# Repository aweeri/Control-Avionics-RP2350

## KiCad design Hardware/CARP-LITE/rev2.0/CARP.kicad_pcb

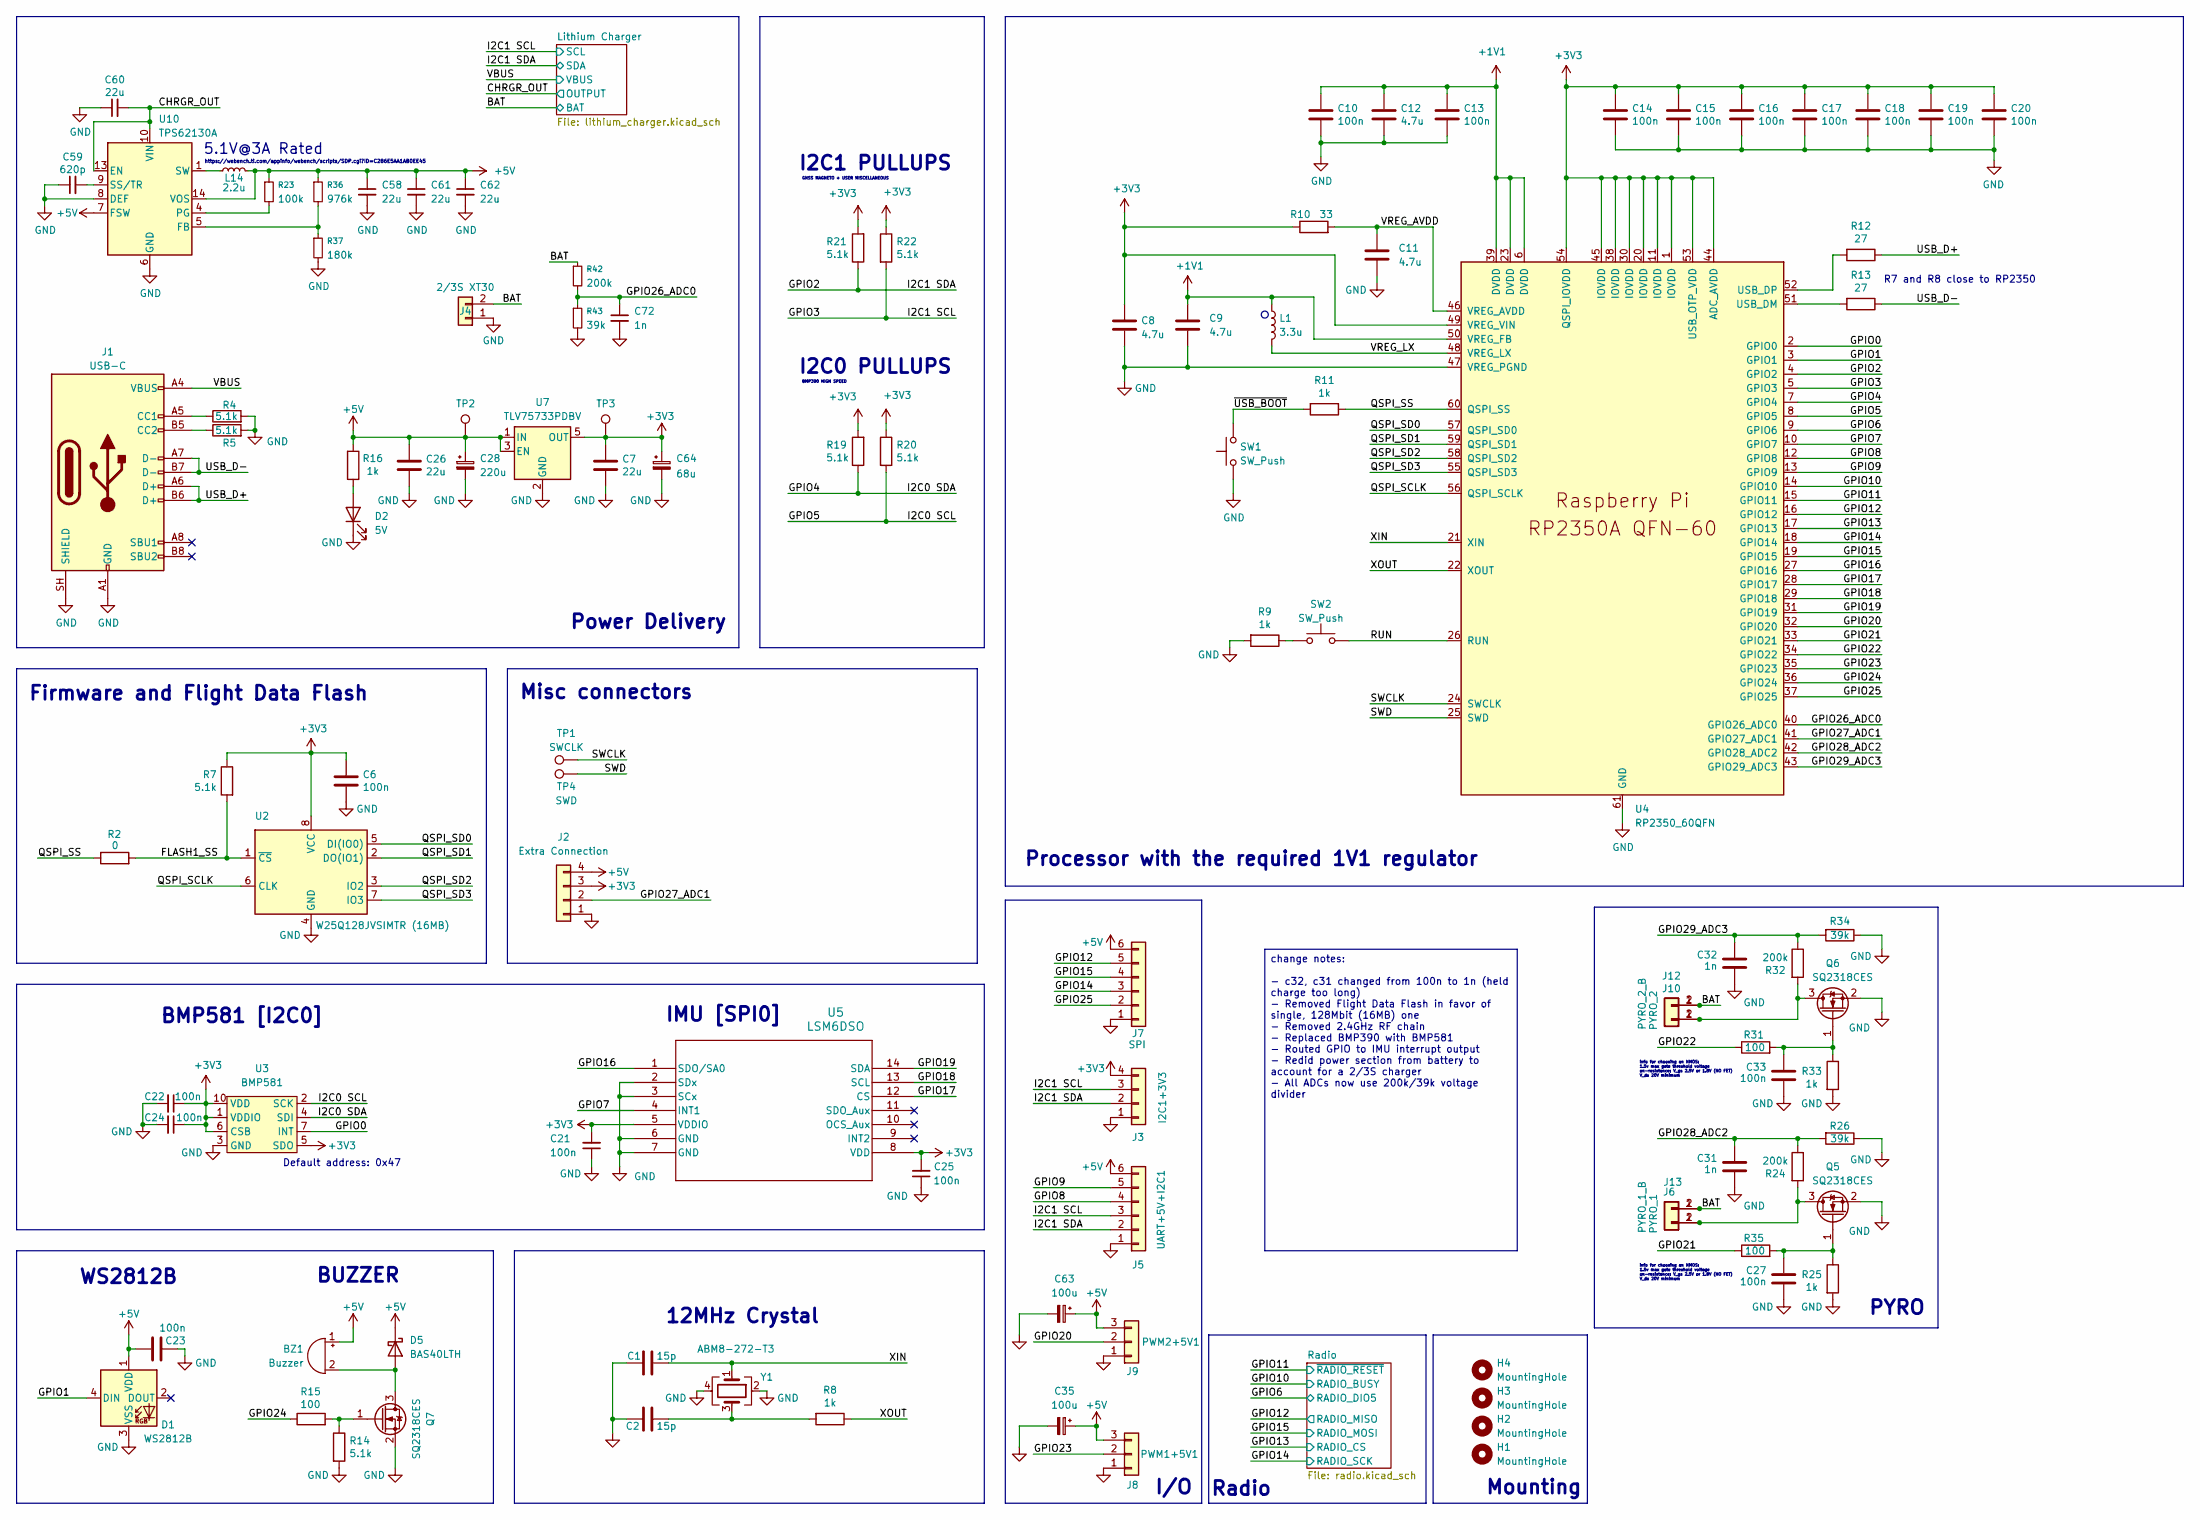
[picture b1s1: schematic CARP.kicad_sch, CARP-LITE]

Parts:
BZ1: Buzzer; Buzzer_12x9.5RM7.6
C1, C2: 15p; C_0402_1005Metric
C6, C10, C13, C14, C15, C16, C17, C18, C19, C20, C21, C22, C23, C24, C25, C27, C33: 100n; C_0402_1005Metric
C7, C26, C58, C60, C61, C62: 22u; C_0805_2012Metric
C8, C9: 4.7u; C_0402_1005Metric_small_pads
C11, C12: 4.7u; C_0402_1005Metric
C28: 220u; CP_EIA-7343-31_Kemet-D
C31, C32, C72: 1n; C_0402_1005Metric
C35, C63: 100u; CP_EIA-6032-28_Kemet-C
C59: 620p; C_0402_1005Metric
C64: 68u; CP_EIA-3528-21_Kemet-B
D1: WS2812B; LED_WS2812B_PLCC4_5.0x5.0mm_P3.2mm
D2: 5V; LED_0805_2012Metric
D5: BAS40LTH; D_SOD-882
H1, H2, H3, H4: MountingHole; MountingHole_3.2mm_M3_DIN965_Pad_TopBottom
J1: USB-C; USB_C_Receptacle_GCT_USB4105-xx-A_16P_TopMnt_Horizontal
J2: Extra Connection; Molex_PicoBlade_53047-0410_1x04_P1.25mm_Vertical
J3: I2C1+3V3; Molex_PicoBlade_53047-0410_1x04_P1.25mm_Vertical
J4: 2/3S XT30; AMASS_XT30PW-M_1x02_P2.50mm_Horizontal
J5: UART+5V+I2C1; Molex_PicoBlade_53047-0610_1x06_P1.25mm_Vertical
J6: PYRO_1; Molex_Nano-Fit_105309-xx02_1x02_P2.50mm_Vertical
J7: SPI; Molex_PicoBlade_53047-0610_1x06_P1.25mm_Vertical
J8: PWM1+5V1; Molex_PicoBlade_53047-0310_1x03_P1.25mm_Vertical
J9: PWM2+5V1; Molex_PicoBlade_53047-0310_1x03_P1.25mm_Vertical
J10: PYRO_2; Molex_Nano-Fit_105309-xx02_1x02_P2.50mm_Vertical
J12: PYRO_2_B; Molex_Nano-Fit_105313-xx02_1x02_P2.50mm_Horizontal
J13: PYRO_1_B; Molex_Nano-Fit_105313-xx02_1x02_P2.50mm_Horizontal
L1: 3.3u; L_pol_2016
L14: 2.2u; L_Coilcraft_XxL4020
Q5, Q6, Q7: SQ2318CES; SOT-23
R2: 0; R_0603_1608Metric
R4, R5, R7, R14, R19, R20, R21, R22: 5.1k; R_0402_1005Metric
R8, R9, R11, R16, R25, R33: 1k; R_0402_1005Metric
R10: 33; R_0402_1005Metric
R12, R13: 27; R_0402_1005Metric
R15, R31, R35: 100; R_0402_1005Metric
R23: 100k; R_0402_1005Metric
R24, R32, R42: 200k; R_0402_1005Metric
R26, R34, R43: 39k; R_0402_1005Metric
R36: 976k; R_0402_1005Metric
R37: 180k; R_0402_1005Metric
SW1, SW2: SW_Push; SW_Push_1P1T_XKB_TS-1187A
TP1: SWCLK; TestPoint_Pad_D1.5mm
TP2, TP3: TestPoint; TestPoint_Pad_D1.5mm
TP4: SWD; TestPoint_Pad_D1.5mm
U2: W25Q128JVSIMTR (16MB); SOIC-8_5.3x5.3mm_P1.27mm
U3: BMP581; 10LGA_2X2X0p75_BOS
U4: RP2350_60QFN; RP2350-QFN-60-1EP_7x7_P0.4mm_EP3.4x3.4mm_ThermalVias
U5: LSM6DSO; LGA-14L_2P5X3X0P86_STM
U7: TLV75733PDBV; SOT-23-5
U10: TPS62130A; VQFN-16-1EP_3x3mm_P0.5mm_EP1.68x1.68mm_ThermalVias
Y1: ABM8-272-T3; Crystal_SMD_3225-4Pin_3.2x2.5mm

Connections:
+1V1: C9.1, C10.1, C12.1, C13.1, L1.1, U4.6 (DVDD), U4.23 (DVDD), U4.39 (DVDD), U4.50 (VREG_FB)
+3V3: C6.1, C7.1, C8.1, C14.1, C15.1, C16.1, C17.1, C18.1, C19.1, C20.1, C21.2, C22.1, C24.1, C25.2, C64.1, J2.3, J3.4, R7.1, R10.1, R19.2, R20.1, R21.2, R22.1, TP3.1 (1_1), U2.8 (VCC), U3.1 (VDDIO), U3.5 (SDO), U3.6 (CSB), U3.10 (VDD), U4.1 (IOVDD), U4.11 (IOVDD), U4.20 (IOVDD), U4.30 (IOVDD), U4.38 (IOVDD), U4.44 (ADC_AVDD), U4.45 (IOVDD), U4.49 (VREG_VIN), U4.53 (USB_OTP_VDD), U4.54 (QSPI_IOVDD), U5.5 (VDDIO), U5.8 (VDD), U7.5 (OUT); also elsewhere on the board
+5V: BZ1.1 (+), C23.1, C26.1, C28.1, C35.1, C58.1, C61.1, C62.1, C63.1, D1.1 (VDD), D5.1 (K), J2.4, J5.6, J7.6, J8.3, J9.3, L14.2, R16.2, R23.1, R36.1, TP2.1 (1_1), U7.1 (IN), U7.3 (EN), U10.7 (FSW), U10.14 (VOS)
/BAT: J4.2, J6.1, J10.1, J12.2, J13.2, R42.1; also elsewhere on the board
/CHRGR_OUT: C60.2, U10.10 (VIN), U10.11 (VIN), U10.12 (VIN), U10.13 (EN); also elsewhere on the board
/FLASH1_SS: R2.2, R7.2, U2.1 (~CS)
/GPIO0: U3.7 (INT), U4.2 (GPIO0)
/GPIO1: D1.4 (DIN), U4.3 (GPIO1)
/GPIO2: J3.2, J5.2, R21.1, U4.4 (GPIO2); also elsewhere on the board
/GPIO3: J3.3, J5.3, R22.2, U4.5 (GPIO3); also elsewhere on the board
/GPIO4: R19.1, U3.4 (SDI), U4.7 (GPIO4)
/GPIO5: R20.2, U3.2 (SCK), U4.8 (GPIO5)
/GPIO6: U4.9 (GPIO6); also elsewhere on the board
/GPIO7: U4.10 (GPIO7), U5.4 (INT1)
/GPIO8: J5.4, U4.12 (GPIO8)
/GPIO9: J5.5, U4.13 (GPIO9)
/GPIO10: U4.14 (GPIO10); also elsewhere on the board
/GPIO11: U4.15 (GPIO11); also elsewhere on the board
/GPIO12: J7.5, U4.16 (GPIO12); also elsewhere on the board
/GPIO13: U4.17 (GPIO13); also elsewhere on the board
/GPIO14: J7.3, U4.18 (GPIO14); also elsewhere on the board
/GPIO15: J7.4, U4.19 (GPIO15); also elsewhere on the board
/GPIO16: U4.27 (GPIO16), U5.1 (SDO/SA0)
/GPIO17: U4.28 (GPIO17), U5.12 (CS)
/GPIO18: U4.29 (GPIO18), U5.13 (SCL)
/GPIO19: U4.31 (GPIO19), U5.14 (SDA)
/GPIO20: J9.2, U4.32 (GPIO20)
/GPIO21: R35.1, U4.33 (GPIO21)
/GPIO22: R31.1, U4.34 (GPIO22)
/GPIO23: J8.2, U4.35 (GPIO23)
/GPIO24: R15.1, U4.36 (GPIO24)
/GPIO26_ADC0: C72.1, R42.2, R43.1, U4.40 (GPIO26_ADC0)
/GPIO27_ADC1: J2.2, U4.41 (GPIO27_ADC1)
/GPIO28_ADC2: C31.2, R24.1, R26.2, U4.42 (GPIO28_ADC2)
/GPIO29_ADC3: C32.2, R32.1, R34.2, U4.43 (GPIO29_ADC3)
/QSPI_SCLK: U2.6 (CLK), U4.56 (QSPI_SCLK)
/QSPI_SD0: U2.5 (DI(IO0)), U4.57 (QSPI_SD0)
/QSPI_SD1: U2.2 (DO(IO1)), U4.59 (QSPI_SD1)
/QSPI_SD2: U2.3 (IO2), U4.58 (QSPI_SD2)
/QSPI_SD3: U2.7 (IO3), U4.55 (QSPI_SD3)
/QSPI_SS: R2.1, R11.1, U4.60 (QSPI_SS)
/RUN: SW2.2, U4.26 (RUN)
/SWCLK: TP1.1 (1_1), U4.24 (SWCLK)
/SWD: TP4.1 (1_1), U4.25 (SWD)
/USB_D+: J1.A6 (D+), J1.B6 (D+), R12.1
/USB_D-: J1.A7 (D-), J1.B7 (D-), R13.1
/VBUS: J1.A4 (VBUS), J1.A9 (VBUS), J1.B4 (VBUS), J1.B9 (VBUS); also elsewhere on the board
/VREG_AVDD: C11.1, R10.2, U4.46 (VREG_AVDD)
/VREG_LX: L1.2, U4.48 (VREG_LX)
/XIN: C1.1, U4.21 (XIN), Y1.1
/XOUT: R8.1, U4.22 (XOUT)
/~USB_BOOT: R11.2, SW1.2
unnamed: BZ1.2 (-), D5.2 (A), Q7.3 (D)
unnamed: C2.1, R8.2, Y1.3
unnamed: D2.2 (A), R16.1
unnamed: J1.A5 (CC1), R4.1
unnamed: J1.B5 (CC2), R5.1
unnamed: J10.2, J12.1, Q6.3 (D), R32.2
unnamed: J6.2, J13.1, Q5.3 (D), R24.2
unnamed: L14.1, U10.1 (SW), U10.2 (SW), U10.3 (SW)
unnamed: C27.2, Q5.1 (G), R25.1, R35.2
unnamed: C33.2, Q6.1 (G), R31.2, R33.1
unnamed: Q7.1 (G), R14.1, R15.2
unnamed: R9.1, SW2.1
unnamed: R13.2, U4.51 (USB_DM)
unnamed: R12.2, U4.52 (USB_DP)
unnamed: R36.2, R37.1, U10.5 (FB)
unnamed: R23.2, U10.4 (PG)
unnamed: C59.2, U10.9 (SS/TR)

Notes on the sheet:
BUZZER
5.1V@3A Rated
PYRO
info for choosing an NMOS: 1.5v max gate threshold voltage on-resistance: V_gs 2.5V or 1.8V (NO FET) V_ds 20V minimum
https://webench.ti.com/appinfo/webench/scripts/SDP.cgi?ID=C286E5AA1AB0EE45
Misc connectors
I2C1 PULLUPS
I2C0 PULLUPS
Firmware and Flight Data Flash
GNSS MAGNETO + USER MISCELLANEOUS
Radio
WS2812B
R7 and R8 close to RP2350
IMU [SPI0]
Default address: 0x47
I/O
Mounting
BMP581 [I2C0]
BMP390 HIGH SPEED
12MHz Crystal
Power Delivery
Processor with the required 1V1 regulator
change notes: - c32, c31 changed from 100n to 1n (held charge too long) - Removed Flight Data Flash in favor of single, 128Mbit (16MB) one - Removed 2.4GHz RF chain - Replaced BMP390 with BMP581 - Routed GPIO to IMU interrupt output - Redid power section from battery to account for a 2/3S charger -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

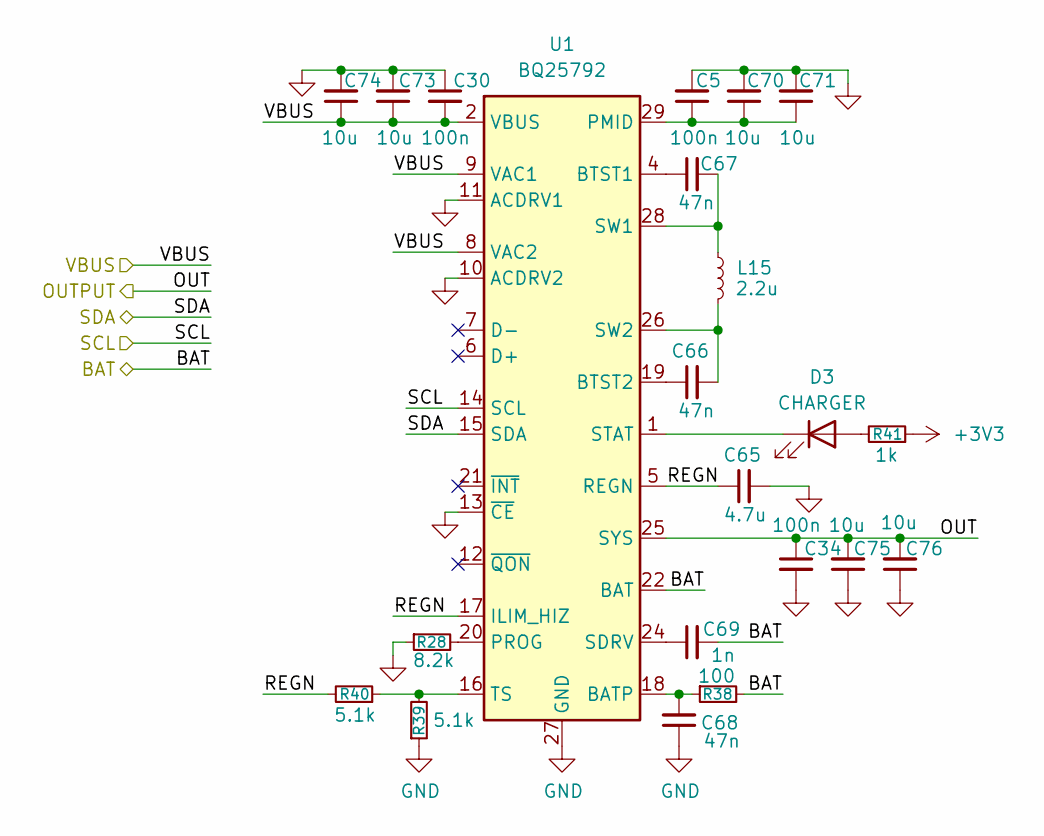
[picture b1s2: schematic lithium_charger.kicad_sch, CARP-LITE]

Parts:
C5, C30, C34: 100n; C_0402_1005Metric
C65: 4.7u; C_0603_1608Metric
C66, C67, C68: 47n; C_0402_1005Metric
C69: 1n; C_0402_1005Metric
C70, C71, C73, C74, C75, C76: 10u; C_0805_2012Metric
D3: CHARGER; LED_0805_2012Metric
L15: 2.2u; L_Coilcraft_XFL2010
R28: 8.2k; R_0402_1005Metric
R38: 100; R_0402_1005Metric
R39, R40: 5.1k; R_0402_1005Metric
R41: 1k; R_0402_1005Metric
U1: BQ25792; Texas_RQM0029A_VQFN-29_4x4mm_P0.4mm

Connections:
+3V3: R41.1; also elsewhere on the board
/BAT: C69.2, R38.2, U1.22 (BAT), U1.23 (BAT); also elsewhere on the board
/CHRGR_OUT: C34.1, C75.2, C76.2, U1.25 (SYS); also elsewhere on the board
/GPIO2: U1.15 (SDA); also elsewhere on the board
/GPIO3: U1.14 (SCL); also elsewhere on the board
/Lithium Charger/REGN: C65.1, R40.2, U1.5 (REGN), U1.17 (ILIM_HIZ)
/VBUS: C30.2, C73.1, C74.1, U1.2 (VBUS), U1.3 (VBUS), U1.8 (VAC2), U1.9 (VAC1); also elsewhere on the board
unnamed: D3.2 (A), R41.2
unnamed: D3.1 (K), U1.1 (STAT)
unnamed: C68.2, R38.1, U1.18 (BATP)
unnamed: C67.1, U1.4 (BTST1)
unnamed: C66.1, U1.19 (BTST2)
unnamed: C5.1, C70.1, C71.1, U1.29 (PMID)
unnamed: R28.2, U1.20 (PROG)
unnamed: C69.1, U1.24 (SDRV)
unnamed: C67.2, L15.1, U1.28 (SW1)
unnamed: C66.2, L15.2, U1.26 (SW2)
unnamed: R39.2, R40.1, U1.16 (TS)

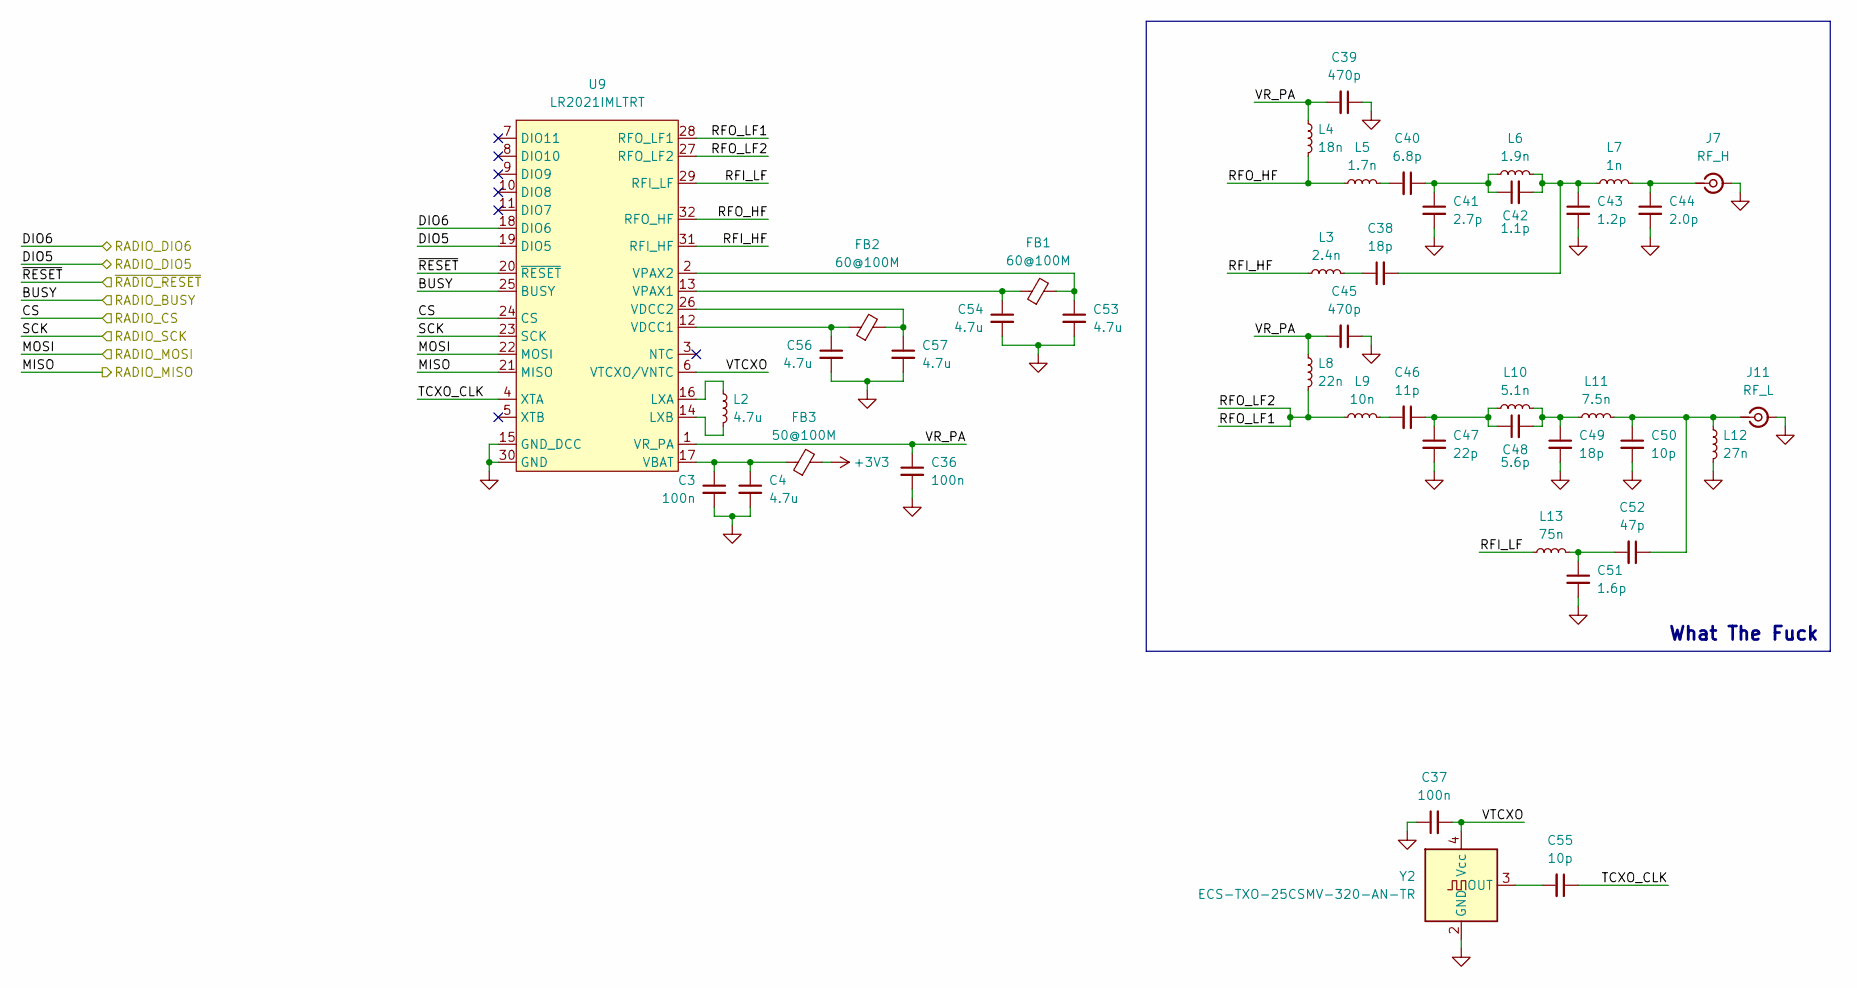
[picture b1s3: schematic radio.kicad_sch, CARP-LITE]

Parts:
C3, C36, C37: 100n; C_0603_1608Metric
C4, C53, C54, C56, C57: 4.7u; C_0603_1608Metric
C38, C49: 18p; C_0402_1005Metric
C39, C45: 470p; C_0402_1005Metric
C40: 6.8p; C_0402_1005Metric
C41: 2.7p; C_0402_1005Metric
C42: 1.1p; C_0402_1005Metric
C43: 1.2p; C_0402_1005Metric
C44: 2.0p; C_0402_1005Metric
C46: 11p; C_0402_1005Metric
C47: 22p; C_0402_1005Metric
C48: 5.6p; C_0402_1005Metric
C50, C55: 10p; C_0402_1005Metric
C51: 1.6p; C_0402_1005Metric
C52: 47p; C_0402_1005Metric
FB1, FB2: 60@100M; L_0603_1608Metric
FB3: 50@100M; L_0603_1608Metric
J7: RF_H; U.FL_Hirose_U.FL-R-SMT-1_Vertical
J11: RF_L; U.FL_Hirose_U.FL-R-SMT-1_Vertical
L2: 4.7u; L_1008_2520Metric
L3: 2.4n; L_0402_1005Metric
L4: 18n; L_0402_1005Metric
L5: 1.7n; L_0402_1005Metric
L6: 1.9n; L_0402_1005Metric
L7: 1n; L_0402_1005Metric
L8: 22n; L_0402_1005Metric
L9: 10n; L_0402_1005Metric
L10: 5.1n; L_0402_1005Metric
L11: 7.5n; L_0402_1005Metric
L12: 27n; L_0402_1005Metric
L13: 75n; L_0402_1005Metric
U9: LR2021IMLTRT; QFN-32-1EP_5x5mm_P0.5mm_EP3.7x3.7mm_ThermalVias
Y2: ECS-TXO-25CSMV-320-AN-TR; Oscillator_SMD_ECS_2520MV-xxx-xx-4Pin_2.5x2.0mm

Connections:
+3V3: FB3.2; also elsewhere on the board
/GPIO6: U9.19 (DIO5); also elsewhere on the board
/GPIO10: U9.25 (BUSY); also elsewhere on the board
/GPIO11: U9.20 (~RESET); also elsewhere on the board
/GPIO12: U9.21 (MISO); also elsewhere on the board
/GPIO13: U9.24 (CS); also elsewhere on the board
/GPIO14: U9.23 (SCK); also elsewhere on the board
/GPIO15: U9.22 (MOSI); also elsewhere on the board
/Radio/RFI_LF: L13.1, U9.29 (RFI_LF)
/Radio/RFO_LF1: L8.2, L9.1, U9.27 (RFO_LF2), U9.28 (RFO_LF1)
/Radio/TCXO_CLK: C55.1, U9.4 (XTA)
/Radio/VR_PA: C36.1, C39.2, C45.2, L4.1, L8.1, U9.1 (VR_PA)
/Radio/VTCXO: C37.2, U9.6 (VTCXO/VNTC), Y2.4 (Vcc)
unnamed: C38.1, L3.2
unnamed: C38.2, C42.2, C43.1, L6.2, L7.1
unnamed: C40.1, C41.1, C42.1, L6.1
unnamed: C40.2, L5.2
unnamed: C46.1, C47.1, C48.1, L10.1
unnamed: C46.2, L9.2
unnamed: C48.2, C49.1, L10.2, L11.1
unnamed: C51.1, C52.2, L13.2
unnamed: C50.1, C52.1, J11.1 (In), L11.2, L12.1
unnamed: L3.1, U9.31 (RFI_HF)
unnamed: L4.2, L5.1, U9.32 (RFO_HF)
unnamed: L2.1, U9.16 (LXA)
unnamed: L2.2, U9.14 (LXB)
unnamed: C3.1, C4.1, FB3.1, U9.17 (VBAT)
unnamed: C56.1, FB2.1, U9.12 (VDCC1)
unnamed: C57.1, FB2.2, U9.26 (VDCC2)
unnamed: C54.1, FB1.1, U9.13 (VPAX1)
unnamed: C53.1, FB1.2, U9.2 (VPAX2)
unnamed: C55.2, Y2.3 (OUT)

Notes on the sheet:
What The Fuck

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
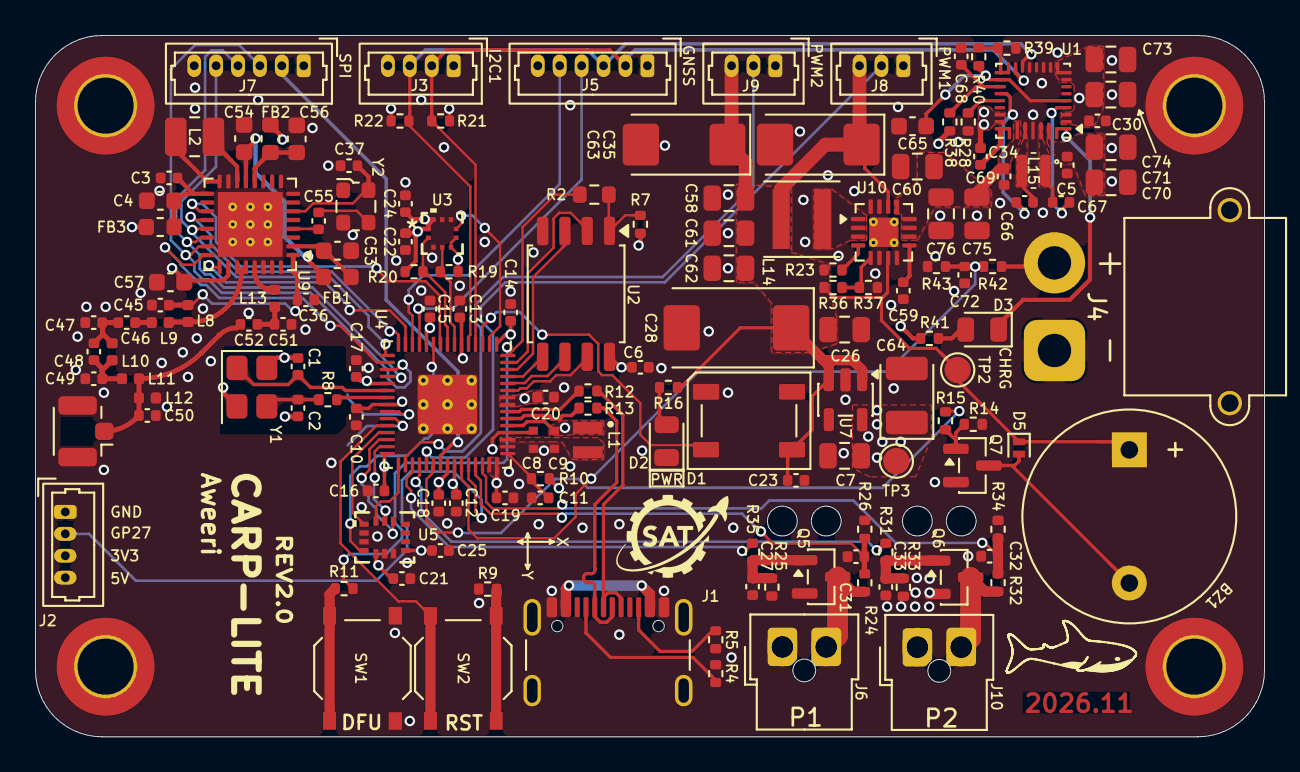
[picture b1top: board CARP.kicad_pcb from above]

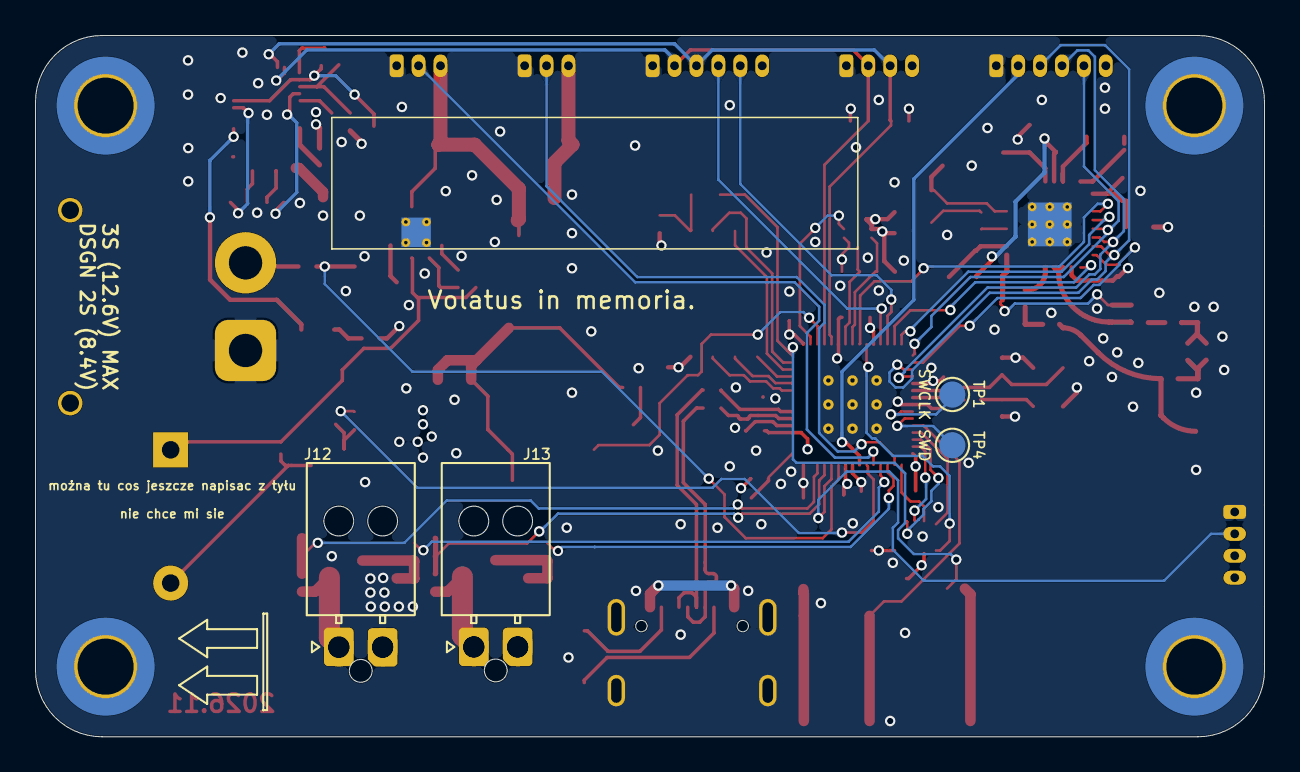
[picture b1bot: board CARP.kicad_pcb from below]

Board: 4 copper layers, 70.1 x 40.0 mm, 157 parts (4 on the bottom side), 101 nets.

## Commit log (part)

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2026-06-29 stuff
2026-06-29 lite
2026-06-29 power delivery adjust
2026-06-29 adjusted ahead of carplite
2026-06-29 credit
2026-06-29 autogen PDF schematics
2026-06-29 fix permissions
2026-06-29 Auto-generate and update schematic PDFs [skip ci]
2026-06-29 refactor and cleanup
2026-06-29 Add Mounting Hole symbols to schematic and update designators
2026-06-29 Change to cron job at midnight
2026-06-29 Add pyro with continuity checks and critical i/o
2026-06-29 more stuff
2026-06-29 Add TODO notes for footprint optimization and pyro circuit checks
2026-06-30 Add initial todo section to README
2026-06-30 test
2026-06-30 fp changes
2026-06-30 pcb changes
2026-06-30 pwr changes
